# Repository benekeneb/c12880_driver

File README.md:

# C12880MA Sensor Driver Readme

This driver is designed to control a C12880MA spectral sensor using a microcontroller. The sensor measures the light spectrum in the visible and near-infrared regions. The firmware is controlled using a set of commands sent via **UART** with a **baud rate of 115200**.

## Command Set
The following commands are available:

- `start_scan`: Starts the scan procedure with the given integration time and average count.
- `cal_sensor`: Calibrates the sensor. Please cover the sensor before calling this function.
- `read_values`: Prints the last measurement of the sensor to the terminal.
- `set_integration_time [time]`: Sets the integration time of the sensor in microseconds. Adjustment in 400ns steps is possible. Default value is 0ns.
- `set_avg_count [count]`: Sets the average count value of the sensor. Default value is 0.
- `set_adc_data_rate [rate]`: Sets the data-rate of the ADS1115. Possible values in SPS: 8, 16, 32, 64, 128, 250, 475, 860. Default value is 860 SPS.
- `set_adc_mode [mode]`: Sets the conversion mode of the ADS1115. 1: single conversion, 0: continuous conversion.
- `get_integration_time`: Outputs the set integration time.
- `get_avg_count`: Outputs the set average count.
- `get_adc_data_rate`: Outputs the set ADC data-rate.
- `get_adc_mode`: Outputs the set ADC mode.
- `help`: Displays the command set.

## File Structure
- `firmware`: Contains the firmware for the sensor driver.
- `eagle`: Contains the EAGLE files for the sensor driver.
- `matlab`: Contains the MATLAB test script that connects to the driver and continuously scans the sensor, outputting the results to a live plot.
- `results`: Contains several test plots generated using the MATLAB script from experiments with different LEDs.

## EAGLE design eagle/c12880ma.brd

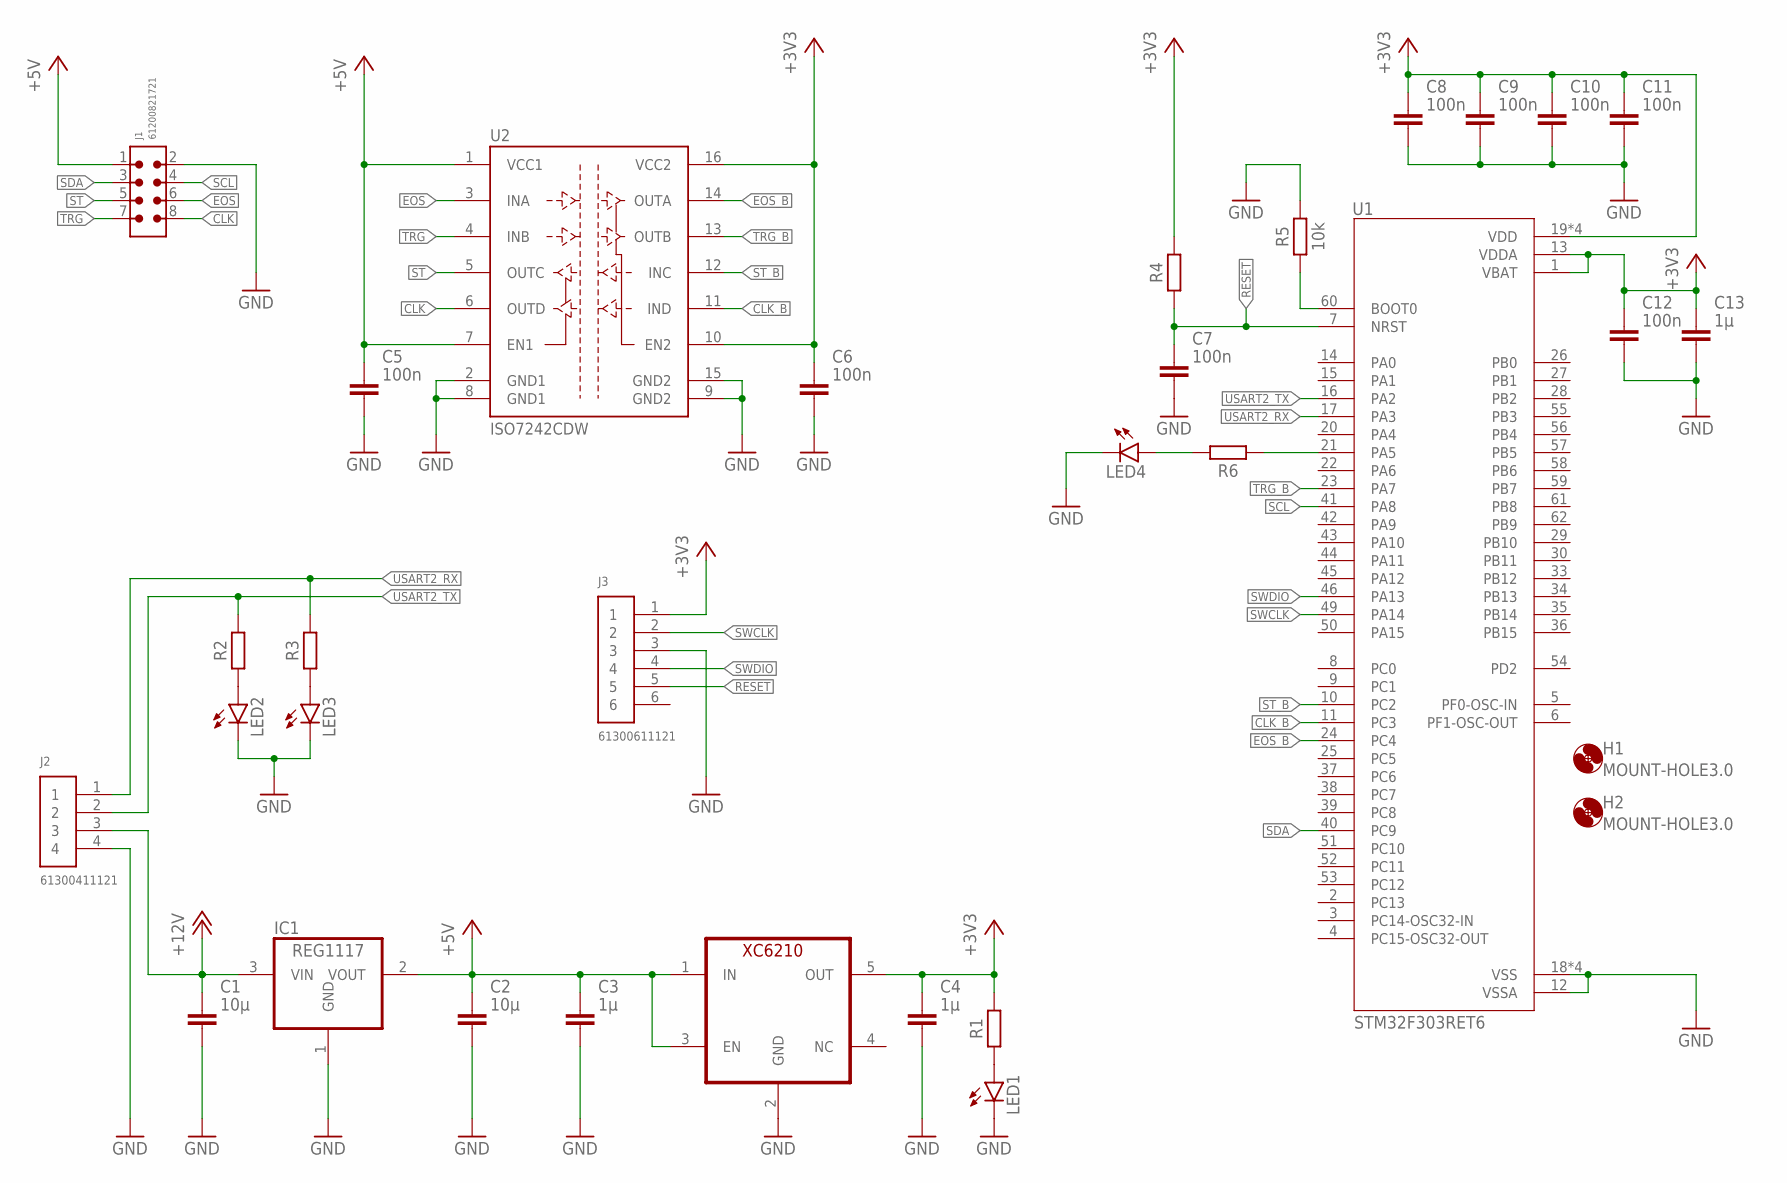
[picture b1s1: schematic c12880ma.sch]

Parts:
C1, C2: 10µ; CAPC1608X85
C3, C4, C13: 1µ; CAPC1608X85
C5, C6, C7, C8, C9, C10, C11, C12: 100n; CAPC1608X85
H1, H2: MOUNT-HOLE3.0; 3,0
IC1: REG1117; SOT223
J1: 61200821721
J2: 61300411121
J3: 61300611121
LED1, LED2, LED3, LED4: LEDCHIP-LED0603; CHIP-LED0603
R1, R2, R3, R4, R6: R_CHIP-0603(1608-METRIC); RESC1608X60
R5: 10k; RESC1608X60
U1: STM32F303RET6; QFP50P1200X1200X160-64N
U2: ISO7242CDW; SO-16DW
U$1: XC6210; SOT23-5

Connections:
+3V3: C4.1, C6.1, C8.1, C9.1, C10.1, C11.1, C12.1, C13.1, J3.1, R1.2, R4.2, U1.1 (VBAT), U1.13 (VDDA), U1.19 (VDD), U1.32 (VDD), U1.48 (VDD), U1.64 (VDD), U2.10 (EN2), U2.16 (VCC2), U$1.5 (OUT)
+5V: C2.1, C3.1, C5.1, IC1.2 (VOUT), J1.1, U2.1 (VCC1), U2.7 (EN1), U$1.1 (IN), U$1.3 (EN)
+12V: C1.1, IC1.3 (VIN), J2.3
CLK: J1.8, U2.6 (OUTD)
CLK_B: U1.11 (PC3), U2.11 (IND)
EOS: J1.6, U2.3 (INA)
EOS_B: U1.24 (PC4), U2.14 (OUTA)
GND: C1.2, C2.2, C3.2, C4.2, C5.2, C6.2, C7.2, C8.2, C9.2, C10.2, C11.2, C12.2, C13.2, IC1.1 (GND), J1.2, J2.4, J3.3, LED1.C, LED2.C, LED3.C, LED4.C, R5.2, U1.12 (VSSA), U1.18 (VSS), U1.31 (VSS), U1.47 (VSS), U1.63 (VSS), U2.2 (GND1), U2.8 (GND1), U2.9 (GND2), U2.15 (GND2), U$1.2 (GND)
unnamed: LED2.A, R2.1
unnamed: LED1.A, R1.1
unnamed: LED3.A, R3.1
unnamed: R5.1, U1.60 (BOOT0)
unnamed: R6.1, U1.21 (PA5)
unnamed: LED4.A, R6.2
RESET: C7.1, J3.5, R4.1, U1.7 (NRST)
SCL: J1.4, U1.41 (PA8)
SDA: J1.3, U1.40 (PC9)
ST: J1.5, U2.5 (OUTC)
ST_B: U1.10 (PC2), U2.12 (INC)
SWCLK: J3.2, U1.49 (PA14)
SWDIO: J3.4, U1.46 (PA13)
TRG: J1.7, U2.4 (INB)
TRG_B: U1.23 (PA7), U2.13 (OUTB)
USART2_RX: J2.1, R3.2, U1.17 (PA3)
USART2_TX: J2.2, R2.2, U1.16 (PA2)

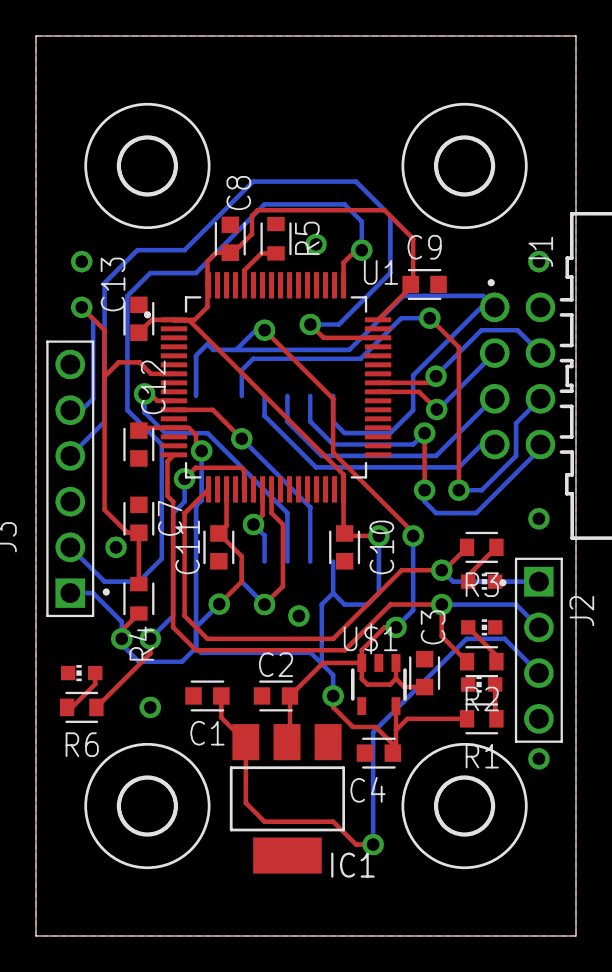
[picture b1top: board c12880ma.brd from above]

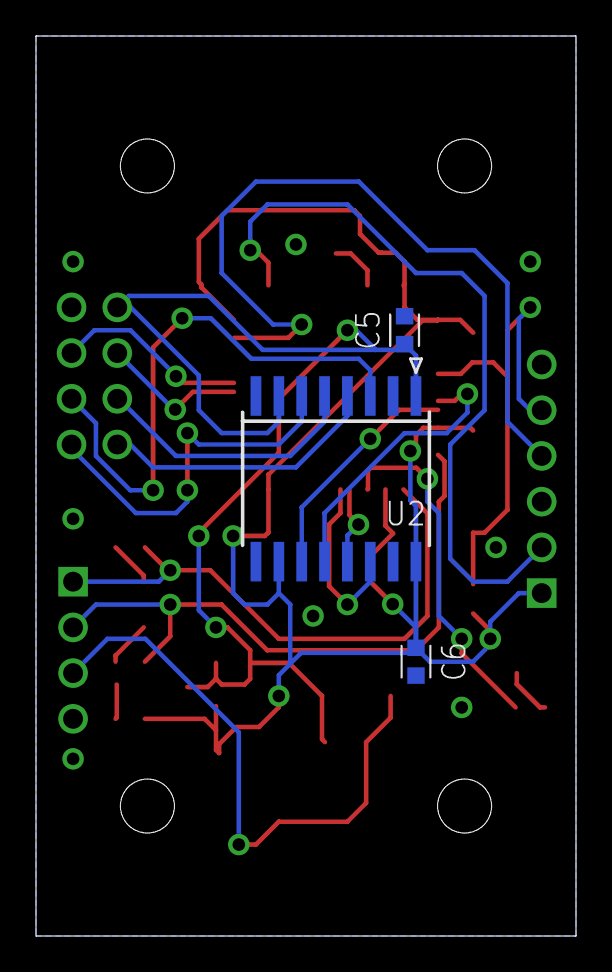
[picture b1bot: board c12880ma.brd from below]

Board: 2 copper layers, 30.0 x 50.0 mm, 34 parts (3 on the bottom side), 25 nets.

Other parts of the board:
H3, H4: MOUNT-HOLE3.0; 3,0

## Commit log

2023-03-28 init commit
2023-03-28 updated pdf schematic

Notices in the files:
parts and their libraries:
Wurth_Connectors_WR-BHD: Copyright: Würth Elektronik
